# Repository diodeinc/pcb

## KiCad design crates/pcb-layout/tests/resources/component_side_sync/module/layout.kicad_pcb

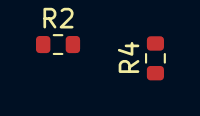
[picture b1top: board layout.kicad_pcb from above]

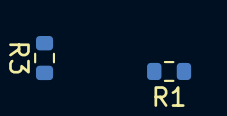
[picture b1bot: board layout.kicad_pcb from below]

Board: 2 copper layers, 4 parts (2 on the bottom side), 2 nets, no tracks yet.

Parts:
R1, R2, R3, R4: SMD 0603 1kOhms +/-10%; R_0603_1608Metric

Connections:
P1: R1.1, R2.1, R3.1, R4.1
P2: R1.2, R2.2, R3.2, R4.2
